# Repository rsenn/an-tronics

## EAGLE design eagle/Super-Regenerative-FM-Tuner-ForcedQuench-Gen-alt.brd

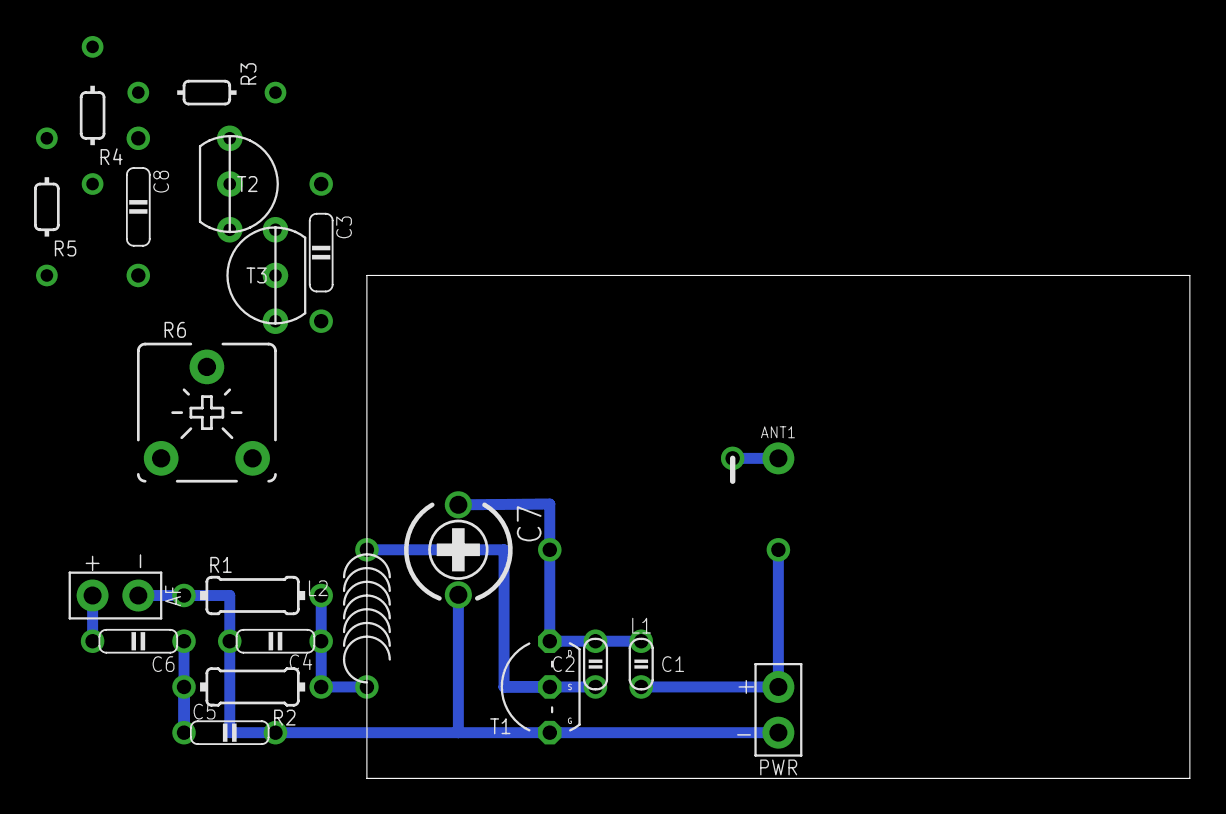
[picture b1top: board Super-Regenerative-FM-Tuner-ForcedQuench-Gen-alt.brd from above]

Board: 2 copper layers, 45.7 x 27.9 mm, 22 parts (0 on the bottom side), 12 nets.

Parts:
AF: SPAD+-+-; SPAD+-
ANT1: ANT; SPAD
C1: 20pF; C025-015X024
C2: 10pF; C025-015X024
C3, C8: 2.7nF; C0750-020X044
C4: 2.7nF; C050-020X044@1
C5: 10nF; C050-020X044@1
C6: 100nF; C050-020X044
C7: 0.04 - 6pF; CTRIMTZ03
L1: 0.1uH; L-08/10-TAP1
L2: 8.2uH; L-04/7-V
PWR: SPAD-+
R1: 10k; 0204/7
R2: 12k; 0204/7
R3: 5.1k; 0202/7-V
R4, R5: 15k; 0202/7-V
R6: 5k; POT-V
T1: BF245A; TO92-GSD
T2, T3: BC557CBE; TO92-CBE

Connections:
GND: AF.1, C4.2, C5.2, C7.1, PWR.1, R1.1, R3.1, R4.1, R5.1, R6.A, T1.1
unnamed: C1.2, C2.1, C7.2, L1.2, T1.3
unnamed: C4.1, L2.2, R1.2, R2.1
unnamed: C8.1, R3.2, T2.C
unnamed: ANT1.1, L1.3
unnamed: C2.2, L2.1, T1.2
unnamed: C5.1, C6.1, R2.2
unnamed: C8.2, R5.2, T3.B
unnamed: AF.2, C6.2
unnamed: C3.2, R6.E, T3.C
unnamed: C3.1, R4.2, T2.B
VCC: C1.1, L1.1, PWR.2, T2.E, T3.E

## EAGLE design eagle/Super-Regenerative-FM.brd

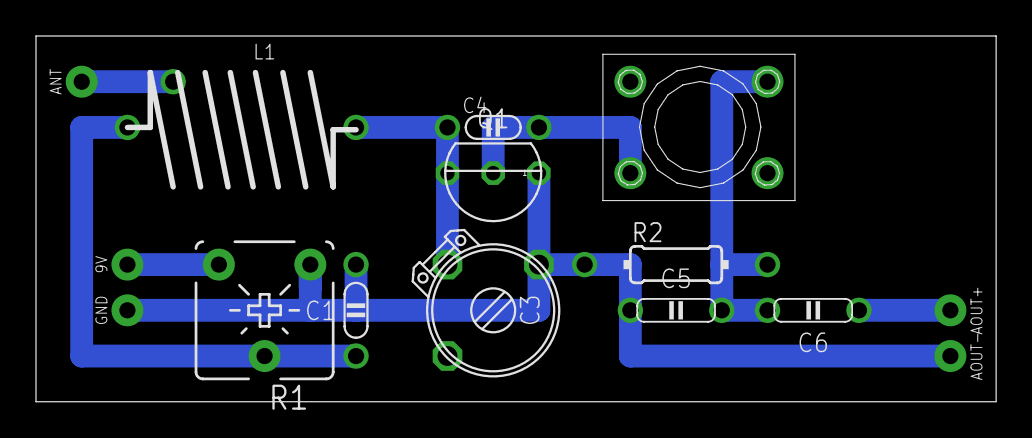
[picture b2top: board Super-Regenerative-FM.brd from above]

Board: 2 copper layers, 53.3 x 20.3 mm, 15 parts (0 on the bottom side), 8 nets.

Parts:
9V: SPAD
ANT: ANT; SPAD
AOUT+: SPAD
AOUT-: SPAD
C1: 1n; C050-020X036/V
C3: 15p; TRIM-2222-808
C4: 4.7pF; C050-020X036
C5: 4.7n; C050-020X044
C6: 100n; C050-020X044
GND: SPAD
L1: 0.22μH; L-08/12-X-TAP1
L2: 3.3μH; L-BODY
Q1: BF245B; TO92
R1: 1kΩ; POT-V
R2: 10kΩ; 0204/10

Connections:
GND: AOUT-.1, C1.2, C3.1, C5.2, GND.1, Q1.1, R1.A, R2.1
unnamed: 9V.1, R1.E
unnamed: C3.2, C4.1, L1.2, Q1.3
unnamed: C1.1, L1.1, R1.S
unnamed: ANT.1, L1.3
unnamed: C4.2, L2.3, Q1.2
unnamed: C5.1, C6.1, L2.2, R2.2
unnamed: AOUT+.1, C6.2

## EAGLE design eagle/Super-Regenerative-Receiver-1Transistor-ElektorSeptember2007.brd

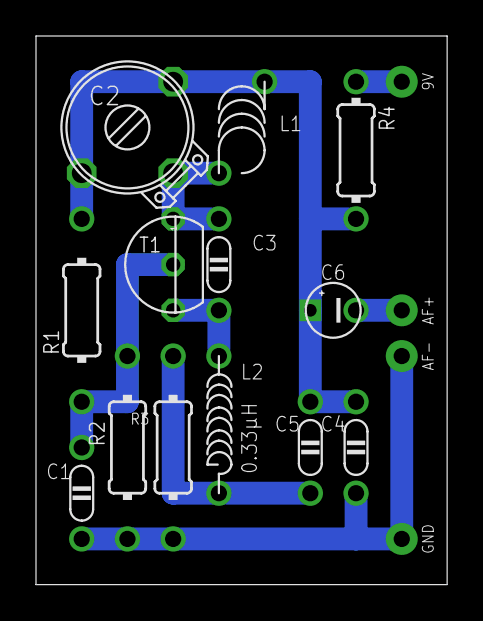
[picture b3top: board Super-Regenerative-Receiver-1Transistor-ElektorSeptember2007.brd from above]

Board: 2 copper layers, 22.8 x 30.5 mm, 17 parts (0 on the bottom side), 8 nets.

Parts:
9V: SPAD
AF+: SPAD
AF-: SPAD
C1, C4, C5: 10n; C050-020X036/V
C2: 22p; TRIM-2222-808
C3: 10p; C050-020X036/V
C6: 10u; E2,5-3
GND: SPAD
L1: 5; L-04-5/5V-X
L2: 0.33μH; L-02/7V
R1, R2, R3: 10kΩ; 0204/10
R4: 10kΩ; 0204/7
T1: 2N3904; TO92

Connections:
GND: AF-.1, C1.2, C4.2, GND.1, R2.1, R3.1
unnamed: C1.1, R1.1, R2.2, T1.2
unnamed: AF+.1, C6.-
unnamed: C5.2, L2.2, R3.2
unnamed: C3.2, L2.1, T1.1
unnamed: C2.2, C3.1, L1.2, T1.3
unnamed: 9V.1, R4.1
unnamed: C2.1, C2.3, C4.1, C5.1, C6.+, L1.1, R1.2, R4.2

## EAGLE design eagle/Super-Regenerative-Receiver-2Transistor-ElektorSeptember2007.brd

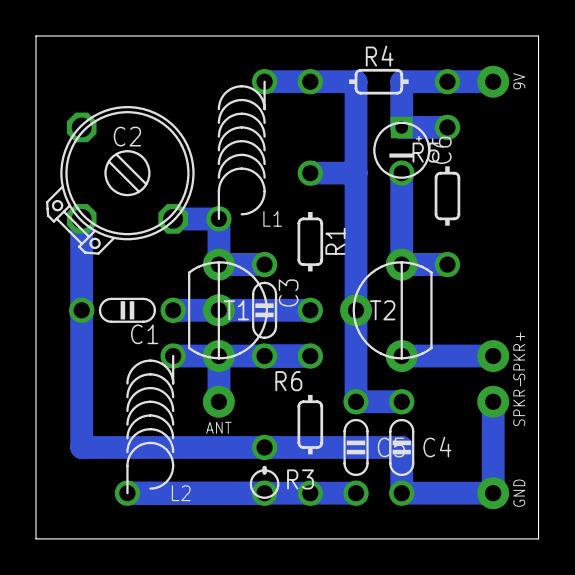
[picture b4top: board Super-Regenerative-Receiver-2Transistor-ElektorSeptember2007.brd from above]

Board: 2 copper layers, 27.9 x 27.9 mm, 20 parts (0 on the bottom side), 9 nets.

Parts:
9V: SPAD
ANT: ANT; SPAD
C1: 10n; C050-020X036
C2: 22p; TRIM-2222-808
C3: 10p; C050-020X036
C4, C5: 10n; C050-020X036/V
C6: 10u; E2,5-3
GND: SPAD
L1: 5; L-04/7V-X
L2: 0.33μH; L-04/7V-X
R1, R4: 10kΩ; 0202/7
R3: 10kΩ; 0202V
R5: 1kΩ; 0202/7-V
R6: 10kΩ; 0202/7-V
SPKR+: SPAD
SPKR-: SPAD
T1: BC547; TO92-CBE
T2: BC557; TO92-CBE-A

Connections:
GND: C1.2, C2.2, C4.2, GND.1, R3.1, SPKR-.1
unnamed: C1.1, R1.1, T1.B
unnamed: C6.-, R5.1, T2.E
unnamed: C5.2, L2.1, R3.2, R6.1
unnamed: ANT.1, C3.2, L2.2, R6.2, T1.E
unnamed: C4.1, C5.1, L1.2, R1.2, R4.2, T2.B
unnamed: 9V.1, C6.+, R4.1, R5.2
unnamed: SPKR+.1, T2.C
unnamed: C2.3, C3.1, L1.1, T1.C

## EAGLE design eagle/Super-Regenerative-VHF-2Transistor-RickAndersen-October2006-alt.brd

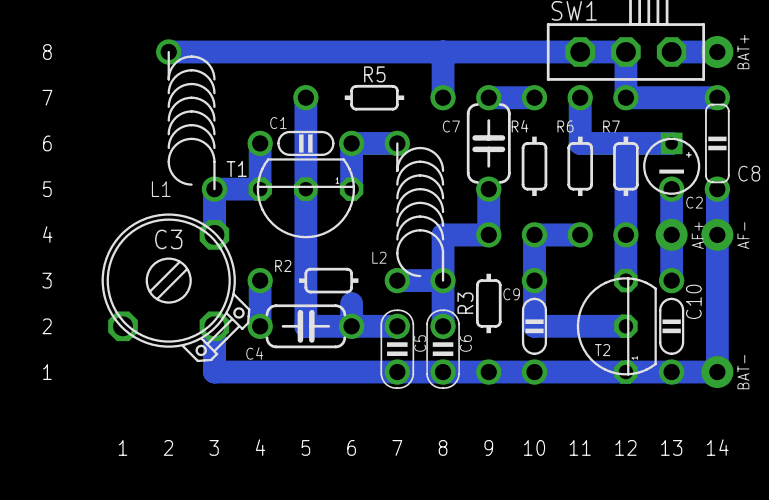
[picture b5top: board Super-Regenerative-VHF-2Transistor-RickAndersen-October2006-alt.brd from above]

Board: 2 copper layers, 25 parts (0 on the bottom side), 12 nets.

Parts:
AF+: SPAD
AF-: SPAD
BAT+: SPAD
BAT-: SPAD
C1: 7pF; C050-020X036
C2: 2.2μF; E2,5-3
C3: 15pF; TRIM-2222-808
C4: 470nF; C050-024X044/V
C5, C6: 1nF; C025-020X036
C7: 470n; C050-024X044/V
C8: 100nF; C050-020X044/V
C9: 10nF; C050-020X036/V
C10: 47nF; C050-020X036
L1, L2: 6; L-04/8V
R2: 12kΩ; 0202/7
R3: 10kΩ; 0202/7
R4: 22kΩ; 0202/7-V
R5: 330kΩ; 0202/7
R6: 220kΩ; 0202/7-V
R7: 4.7kΩ; 0202/7-V
SW1: SL-SW-1P-2T-H; SLSW-1P2T-H
T1, T2: 2N3904; TO92

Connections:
GND: AF-.1, BAT-.1, C3.2, C5.2, C6.2, C8.2, C9.2, C10.2, R3.2, T2.1
unnamed: C1.2, C3.3, L1.1, T1.3
unnamed: C1.1, L2.2, T1.1
unnamed: C7.1, R4.1
unnamed: C4.2, C5.1, R5.2, T1.2
unnamed: C2.+, R6.2, R7.1, T2.3
unnamed: C6.1, C7.2, L2.1, R2.2, R3.1
unnamed: C4.1, R2.1
unnamed: BAT+.1, SW1.1
unnamed: C9.1, R4.2, R6.1, T2.2
unnamed: AF+.1, C2.-, C10.1
VCC: C8.1, L1.2, R5.1, R7.2, SW1.3
